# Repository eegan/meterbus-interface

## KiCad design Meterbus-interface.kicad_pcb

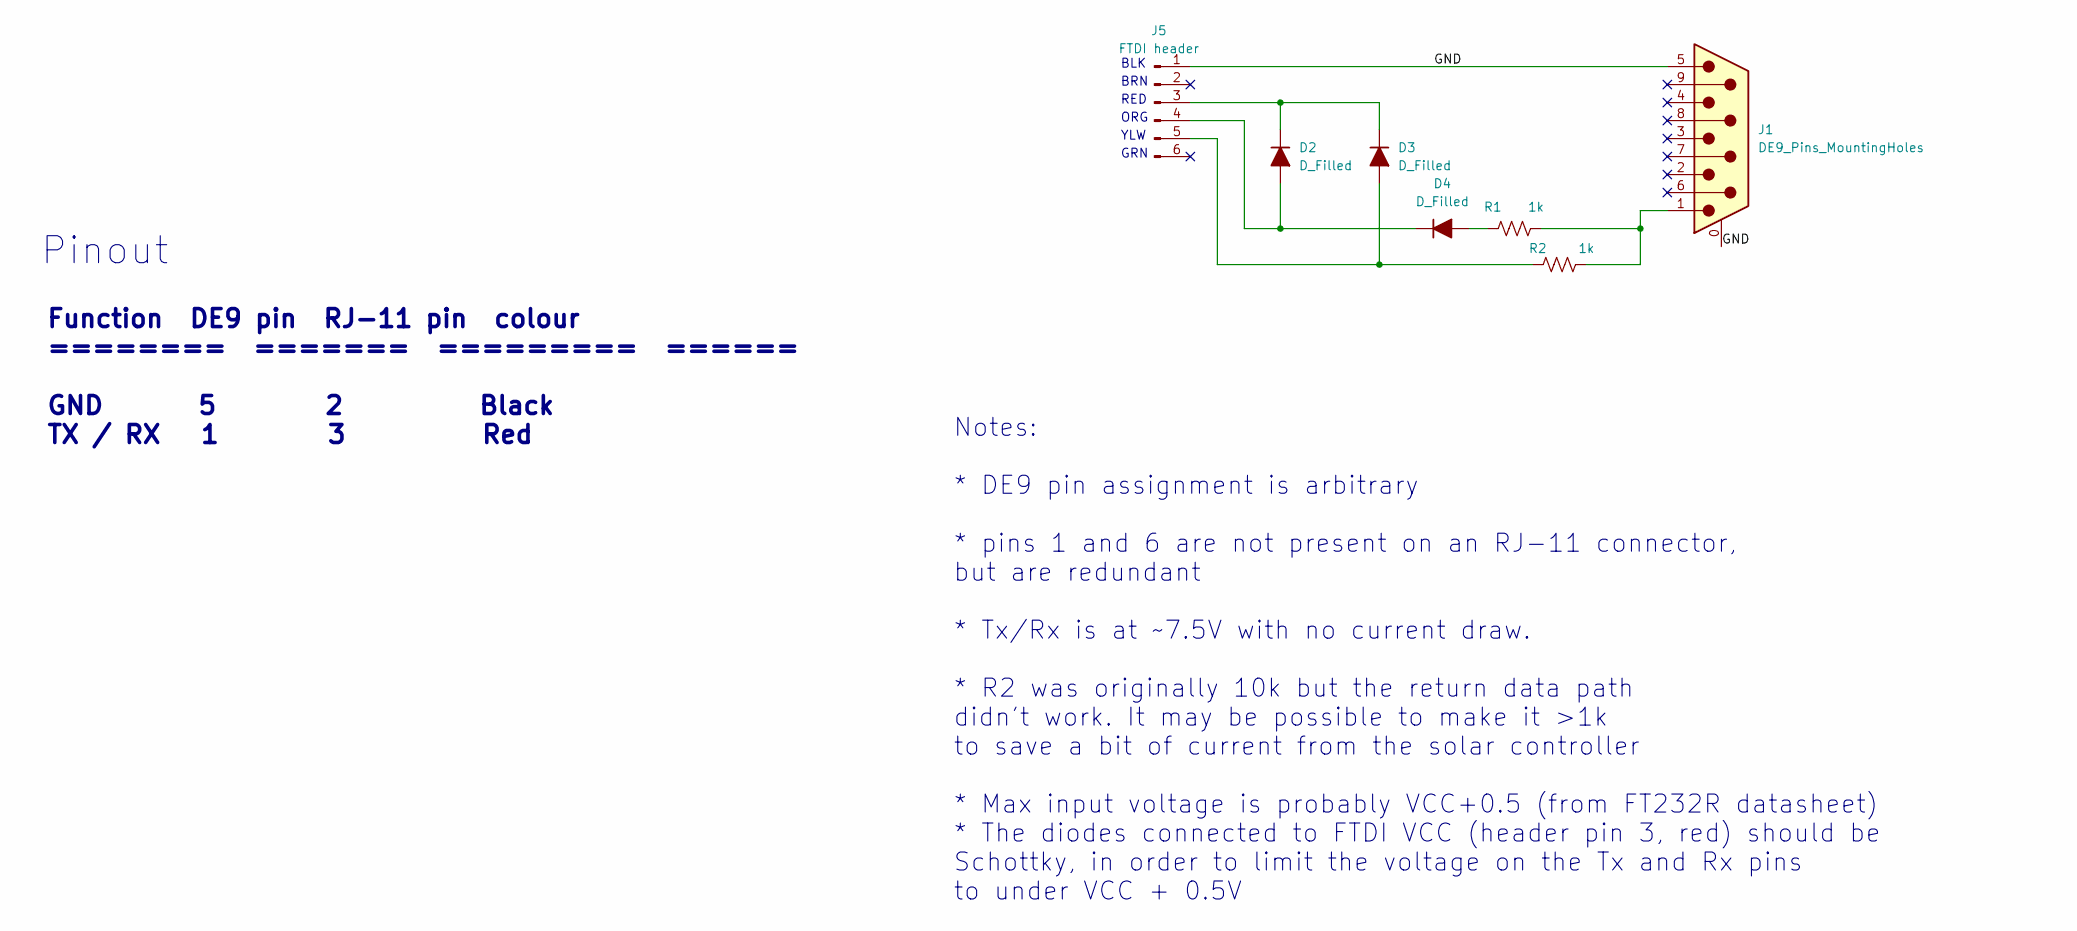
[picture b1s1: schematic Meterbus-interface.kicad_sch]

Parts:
D2, D3, D4: D_Filled; D_DO-35_SOD27_P12.70mm_Horizontal
J1: DE9_Pins_MountingHoles; DSUB-9_Pins_Horizontal_P2.77x2.84mm_EdgePinOffset7.70mm_Hou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
J5: FTDI header; PinHeader_1x06_P2.54mm_Horizontal
R1, R2: 1k; R_Axial_DIN0207_L6.3mm_D2.5mm_P10.16mm_Horizontal

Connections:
/GND: J1.0 (PAD), J1.5, J5.1
unnamed: D2.2 (A), D4.1 (K), J5.4
unnamed: D2.1 (K), D3.1 (K), J5.3
unnamed: D3.2 (A), J5.5, R2.1
unnamed: D4.2 (A), R1.1
unnamed: J1.1, R1.2, R2.2

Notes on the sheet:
Function DE9 pin RJ-11 pin colour ======== ======= ========= ====== GND 5 2 Black TX / RX 1 3 Red
Pinout
ORG
GRN
BLK
YLW
RED
BRN
Notes: * DE9 pin assignment is arbitrary * pins 1 and 6 are not present on an RJ-11 connector, but are redundant * Tx/Rx is at ~7.5V with no current draw. * R2 was originally 10k but the return data path didn't work. It may be possible to make it >1k to save a bit of current from the solar controll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

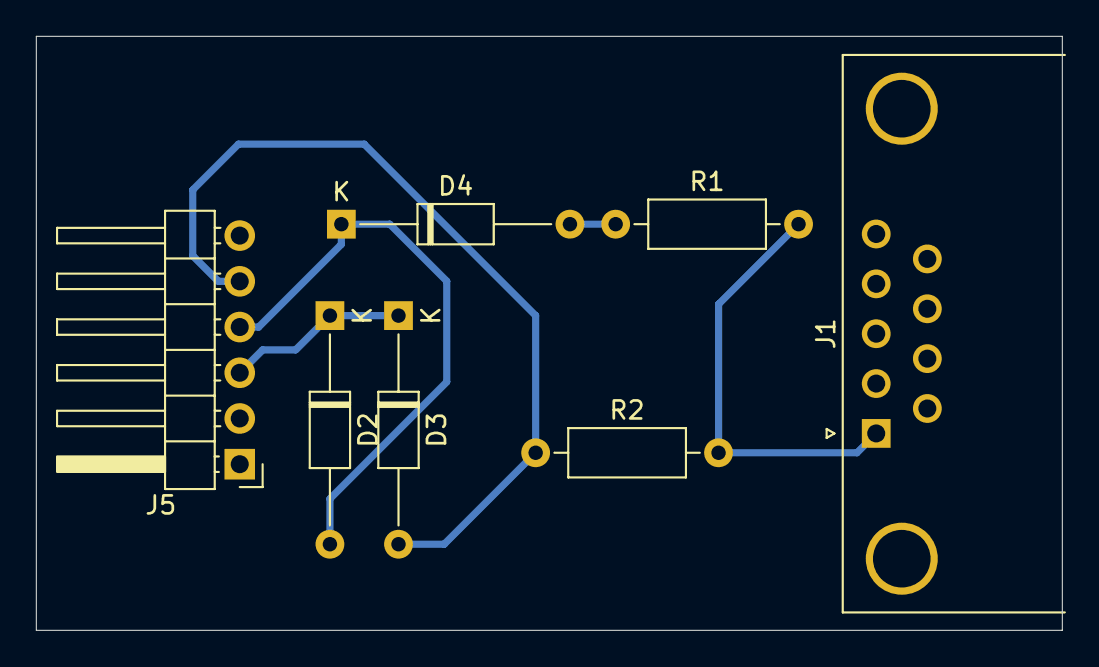
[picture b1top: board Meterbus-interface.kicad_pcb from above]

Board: 2 copper layers, 57.0 x 33.0 mm, 7 parts (0 on the bottom side), 6 nets.

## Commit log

2025-05-09 milling-machine-version
2025-05-09 added
2025-05-12 Change DE-9 from socket to pin type, add copper pour on bottom, reroute, change R2 to 1k
2025-05-13 use mounting hole symbol for dsub connector, and connet shell to ground plane. Remove gerber files from tracking.
